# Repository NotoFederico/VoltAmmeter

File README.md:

# VoltAmmeter

Medidor de tensión y corriente de precisión para fuente de alimentación implementado con placa de desarrollo BLUEPILL (STM32F103)
---

---

### Download
| Latest release | Latest development build |
|----------------|--------------------------|
|  |  |

---

# Contents
- 1 - [Introduction](#1-introduction)
- 2 - [Downloading the application](#2-downloading-the-game-pre-built)
- 3 - [Building the game](#3-building-the-game)
  - 3.1 - [Building prerequisites](#31-building-prerequisites)
  - 3.2 - [Compiling and running](#32-compiling-and-running)
- 4 - [Contributing](#4-contributing)
- 5 - [Licence](#5-licence)

---

# 1. Introduction

Utiliza un módulo ADS1115 (ADC 16 bits) para la lectura diferencial de corriente y la lectura de tensión de una fuente de alimentación regulable de 0V a 60V y de 0A a 5A.
A través de una comunicación I2C los datos son procesados por el microprocesador a través de un simple algoritmo de promedio de muestras.

Está en curso una segunda versión con tecnologia SMD y se está estudiando implementar un algoritmo que obtenga el promedio de manera mas eficiente

---

# 2. Downloading the application

---

# 3. Building the application

## 3.1 Building prerequisites

---

## 3.2 Compiling and running

---

# 4. Contributing

---
# 5. Licence

Pong Game is licensed under the GNU General Public License version 3.

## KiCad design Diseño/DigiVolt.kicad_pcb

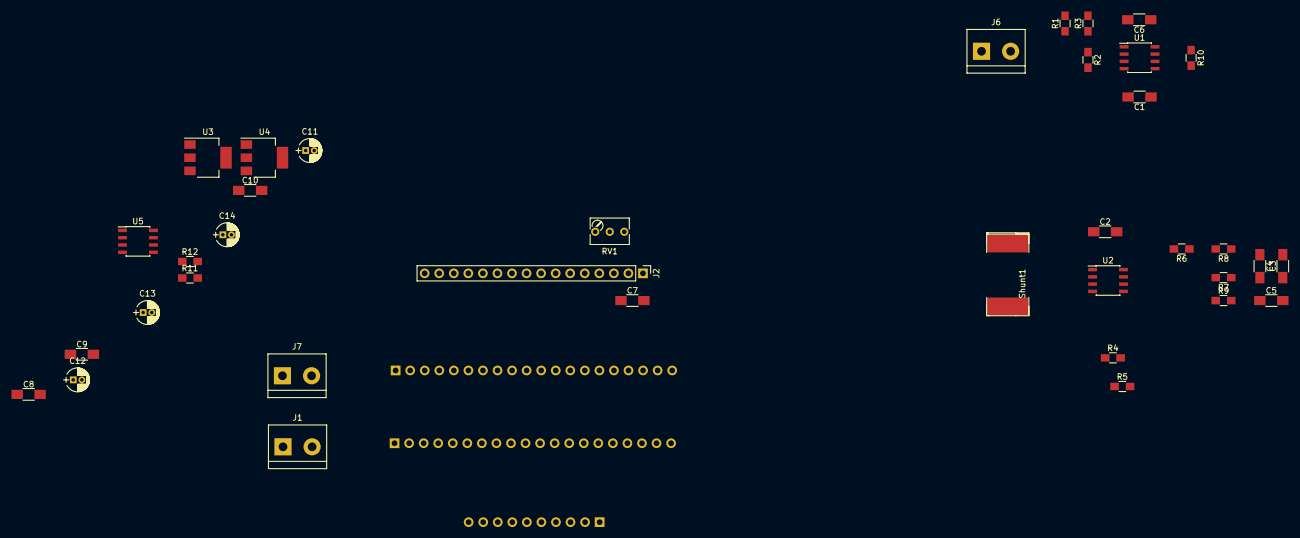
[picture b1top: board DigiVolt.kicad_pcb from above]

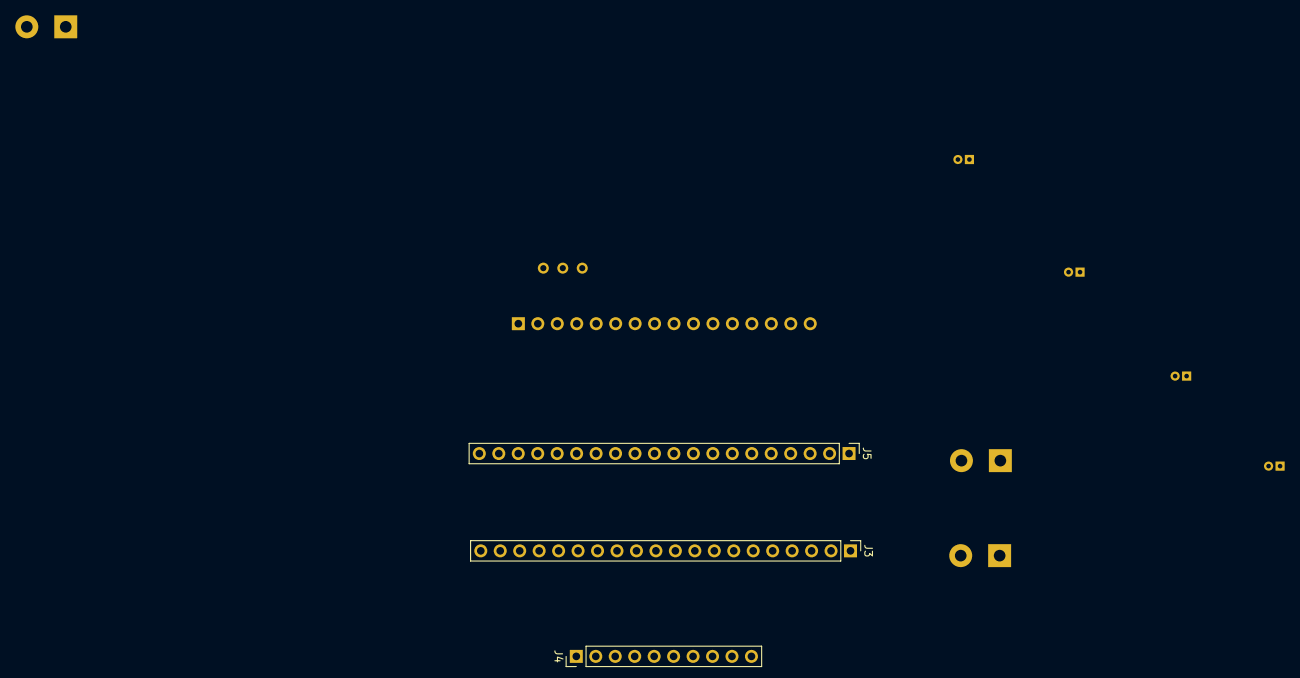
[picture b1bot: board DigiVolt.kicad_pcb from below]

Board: 4 copper layers, 40 parts (3 on the bottom side), 25 nets, no tracks yet.

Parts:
C1, C2, C7, C8, C9, C10: 0.1u; C_1206_HandSoldering
C3, C5: 0.022u; C_1206_HandSoldering
C4: 0.22u; C_1206_HandSoldering
C6: 3.9n; C_1206_HandSoldering
C11: 10uf; CP_Radial_D4.0mm_P1.50mm
C12, C14: 100uF; CP_Radial_D4.0mm_P1.50mm
C13: 10uF; CP_Radial_D4.0mm_P1.50mm
J1: CURRENT; TerminalBlock_bornier-2_P5.08mm
J2: DISPLAY; Socket_Strip_Straight_1x16_Pitch2.54mm
J3: BLUE PILL A; Socket_Strip_Straight_1x20_Pitch2.54mm
J4: ADS1115; Socket_Strip_Straight_1x10_Pitch2.54mm
J5: BLUE PILL B; Socket_Strip_Straight_1x20_Pitch2.54mm
J6: VOLTAGE; TerminalBlock_bornier-2_P5.08mm
J7: POWER; TerminalBlock_bornier-2_P5.08mm
R1: 15k; R_0805_HandSoldering
R2: 1k; R_0805_HandSoldering
R3: 150k; R_0805_HandSoldering
R4, R5: 1.2k; R_0805_HandSoldering
R6, R7: 8.2k; R_0805_HandSoldering
R8, R9: 100; R_0805_HandSoldering
R10: 12k; R_0805_HandSoldering
R11, R12: 10k; R_0805_HandSoldering
RV1: 10k; Potentiometer_Trimmer_Bourns_3266Y
Shunt1: 0.05; SMD-1206_Pol
U1, U2: AD8628; SOIC-8_3.9x4.9mm_Pitch1.27mm
U3: LM1117-3.3; SOT-223-3_TabPin2
U4: LM1117-5.0; SOT-223-3_TabPin2
U5: ‎MCP6241T; SOIC-8_3.9x4.9mm_Pitch1.27mm

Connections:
+3V3: C9.1, C12.1, J3.20, U3.2
+5V: C1.1, C2.2, C7.1, C8.1, C10.2, C14.1, J2.2, J2.15, J4.10, R11.1, RV1.3, U1.7, U2.7, U4.2, U5.7
/ADC_0: C4.2, C5.1, J4.4, R9.1
/ADC_1: C3.2, C4.1, J4.3, R8.1
/ADC_2: C6.1, J4.2, R10.1
/DISPLAY_DB4: J2.11, J5.5
/DISPLAY_DB5: J2.12, J5.6
/DISPLAY_DB6: J2.13, J5.7
/DISPLAY_DB7: J2.14, J5.8
/DISPLAY_ENABLE: J2.6, J5.10
/DISPLAY_RESET: J2.4, J5.9
/DISPLAY_VO: J2.3, RV1.2
/LOAD: J1.1, R4.2, Shunt1.1
/POWER: C11.1, C13.1, J7.1, U3.3, U4.3
/SCL: J3.14, J4.8
/SDA: J3.15, J4.7
/VCM: R6.1, R8.2, U5.2, U5.6
/VOLTAGE: J6.1, R1.1, R3.1
GND: C1.2, C2.1, C3.1, C5.2, C6.2, C7.2, C8.2, C9.2, C10.1, C11.2, C12.2, C13.2, C14.2, J1.2, J2.1, J2.5, J2.16, J3.19, J4.6, J4.9, J5.19, J5.20, J6.2, J7.2, R2.2, R5.2, R12.2, RV1.1, Shunt1.2, U1.4, U2.4, U3.1, U4.1, U5.4
unnamed: R1.2, R2.1, R3.2, U1.3
unnamed: R4.1, R6.2, U2.3
unnamed: R5.1, R7.2, U2.2
unnamed: R7.1, R9.2, U2.6
unnamed: R10.2, U1.2, U1.6
unnamed: R11.2, R12.1, U5.3
